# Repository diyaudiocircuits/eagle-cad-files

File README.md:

eagle-cad-files
===============

A collection of PCB (printed circuit board) designs made with the Eagle CAD program.

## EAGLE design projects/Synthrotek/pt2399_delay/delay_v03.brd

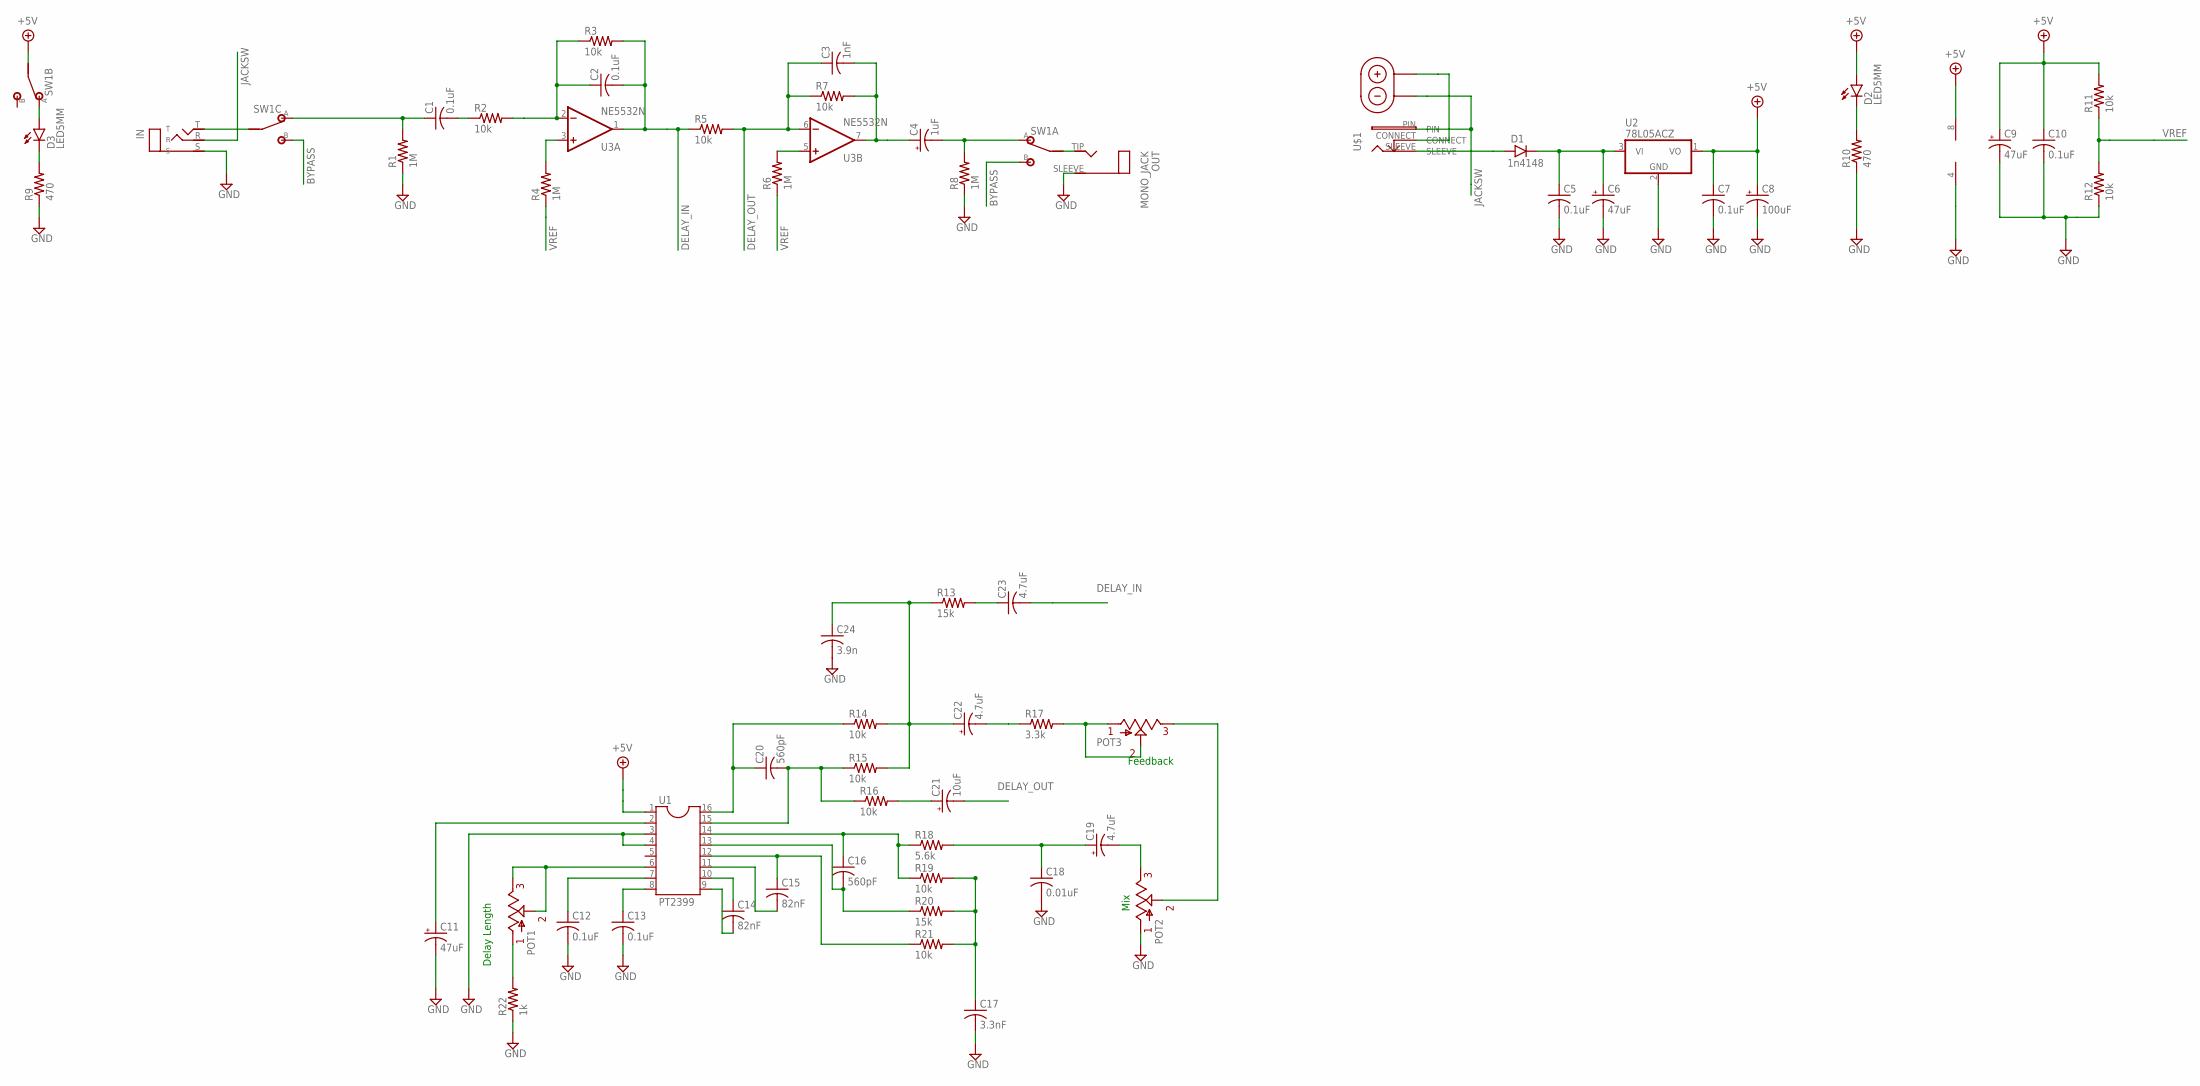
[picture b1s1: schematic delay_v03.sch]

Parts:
C1, C2, C5, C7, C10, C12, C13: 0.1uF; C050-035X075
C3: 1nF; C050-035X075
C4: 1uF; 063_025
C6, C9, C11: 47uF; 063_025
C8: 100uF; 063_025
C14, C15: 82nF; C050-035X075
C16, C20: 560pF; C050-035X075
C17: 3.3nF; C050-035X075
C18: 0.01uF; C050-035X075
C19, C22: 4.7uF; 063_025
C21: 10uF; 063_025
C23: 4.7uF; C050-035X075
C24: 3.9n; C050-035X075
D1: 1n4148; DO41-3
D2, D3: LED5MM
IN: STEREO_JACK
OUT: MONO_JACK
POT1, POT2, POT3: POT
R1, R4, R6, R8: 1M; RESISTOR
R2, R3, R5, R7, R11, R12, R14, R15, R16, R19, R21: 10k; RESISTOR
R9, R10: 470; RESISTOR
R13, R20: 15k; RESISTOR
R17: 3.3k; RESISTOR
R18: 5.6k; RESISTOR
R22: 1k; RESISTOR
SW1: 3PDT
U1: PT2399; SOCKET-16
U2: 78L05ACZ; TO-92
U3: NE5532N; DIL08
U$1: DC_JACK_OFFBOARD
U$2: 9V_BATTERY_CLIP; 9V_BATTERY

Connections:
9V: C5.1, C6.+, D1.C, U2.3 (VI)
BYPASS: SW1.A3 (B), SW1.C3 (B)
C5*: C13.1, U1.8
DELAY_IN: C2.2, C23.2, R3.2, R5.1, U3.1 (OUT)
DELAY_OUT: C3.1, C21.-, R5.2, R7.1, U3.6 (-IN)
DELAY_OUT_UNBUFFERED: R6.2, U3.5 (+IN)
GND: C5.2, C6.-, C7.2, C8.-, C9.-, C10.2, C11.-, C12.2, C13.2, C17.2, C18.2, C24.2, IN.S, OUT.SLEEVE, POT2.1, R1.1, R8.1, R9.1, R10.1, R12.1, R22.1, U1.3, U1.4, U2.2 (GND), U3.4 (V-)
JACKSW: IN.R, U$1.PIN, U$2.9V_BATTERY_-
unnamed: C23.1, R13.2
unnamed: C12.1, U1.7
unnamed: C14.2, U1.9
unnamed: C14.1, U1.10
unnamed: C17.1, R19.2, R20.2, R21.2
unnamed: C15.1, R21.1, U1.12
unnamed: POT1.2, POT1.3, U1.6
unnamed: C11.+, U1.2
unnamed: C1.1, R1.2, SW1.C1 (A)
unnamed: POT1.1, R22.2
unnamed: C16.2, R20.1, U1.13
unnamed: OUT.TIP, SW1.A2 (COM)
unnamed: C20.2, R15.1, R16.1, U1.15
unnamed: C20.1, R14.1, U1.16
unnamed: C18.1, C19.+, R18.2
unnamed: C15.2, U1.11
unnamed: C2.1, R2.2, R3.1, U3.2 (-IN)
unnamed: C19.-, POT2.3
unnamed: C22.+, C24.1, R13.1, R14.2, R15.2
unnamed: C22.-, R17.1
unnamed: C1.2, R2.1
unnamed: POT2.2, POT3.3
unnamed: C21.+, R16.2
unnamed: C16.1, R18.1, R19.1, U1.14
unnamed: D3.A, SW1.B1 (A)
unnamed: C3.2, C4.+, R7.2, U3.7 (OUT)
unnamed: D2.K (C), R10.2
unnamed: D1.A, U$1.SLEEVE
unnamed: IN.T, SW1.C2 (COM)
unnamed: C4.-, R8.2, SW1.A1 (A)
unnamed: U$1.CONNECT, U$2.9V_BATTERY_+
unnamed: D3.K (C), R9.2
unnamed: POT3.1, POT3.2, R17.2
unnamed: R4.2, U3.3 (+IN)
VA: C7.1, C8.+, C9.+, C10.1, D2.A, R11.2, SW1.B2 (COM), U1.1, U2.1 (VO), U3.8 (V+)
VREF: R4.1, R6.1, R11.1, R12.2

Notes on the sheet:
Feedback
Mix
Delay Length

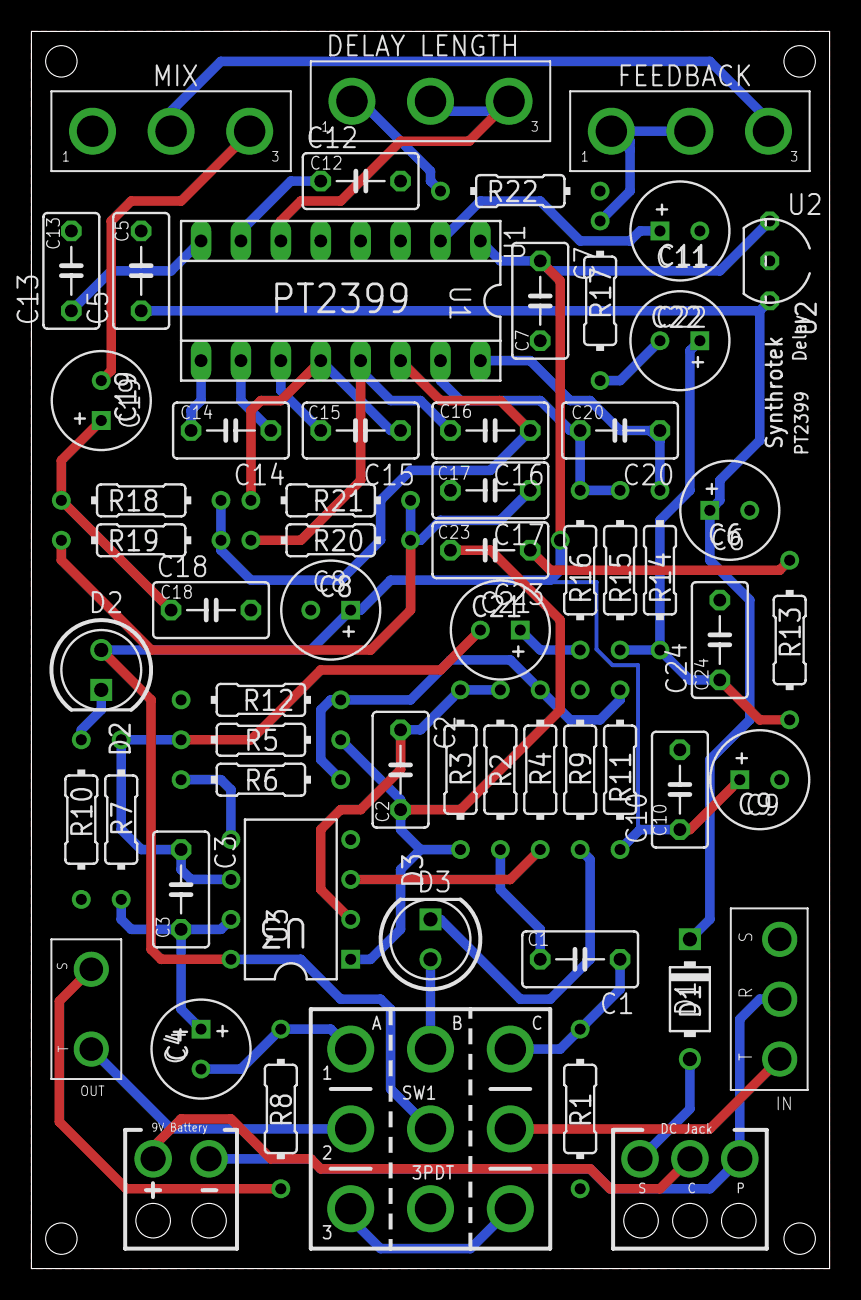
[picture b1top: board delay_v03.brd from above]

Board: 2 copper layers, 50.8 x 78.7 mm, 60 parts (0 on the bottom side), 44 nets.

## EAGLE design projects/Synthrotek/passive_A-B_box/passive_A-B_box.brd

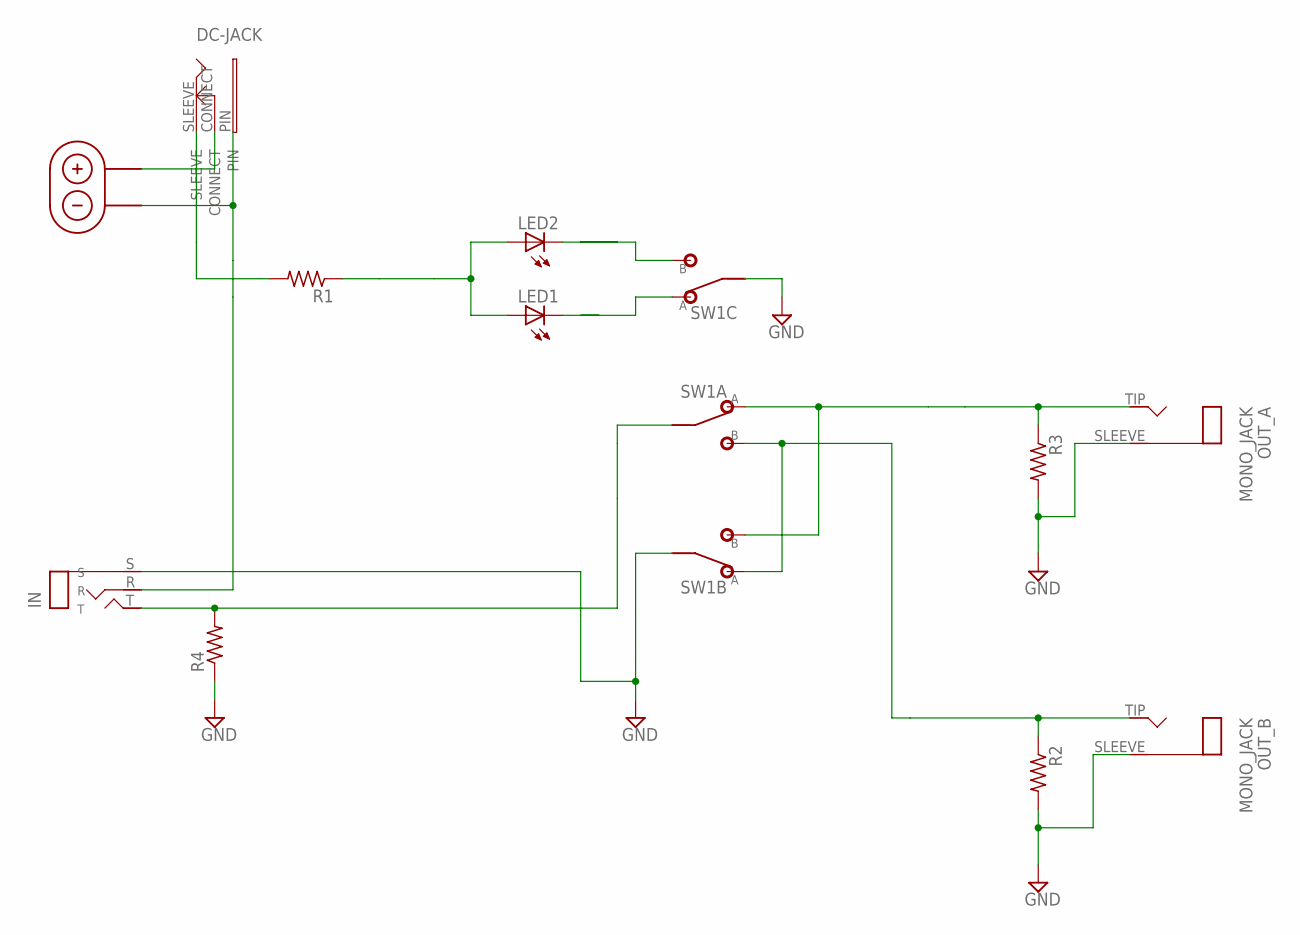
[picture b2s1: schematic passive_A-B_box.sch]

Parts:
DC-JACK: DC_JACK; DC_JACK_OFFBOARD
IN: STEREO_JACK
LED1, LED2: LED5MM
OUT_A: MONO_JACK
OUT_B: MONO_JACK
R1, R2, R3, R4: RESISTOR
SW1: 3PDT
U$4: 9V_BATTERY_CLIP; 9V_BATTERY

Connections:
DC-JACK: DC-JACK.CONNECT, U$4.9V_BATTERY_+
GND: IN.S, OUT_A.SLEEVE, OUT_B.SLEEVE, R2.2, R3.2, R4.1, SW1.B2 (COM), SW1.C2 (COM)
unnamed: IN.T, R4.2, SW1.A2 (COM)
unnamed: DC-JACK.SLEEVE, R1.2
unnamed: LED1.K (C), SW1.C1 (A)
unnamed: LED2.K (C), SW1.C3 (B)
unnamed: LED1.A, LED2.A, R1.1
unnamed: OUT_A.TIP, R3.1, SW1.A1 (A), SW1.B3 (B)
unnamed: OUT_B.TIP, R2.1, SW1.A3 (B), SW1.B1 (A)
unnamed: DC-JACK.PIN, IN.R, U$4.9V_BATTERY_-

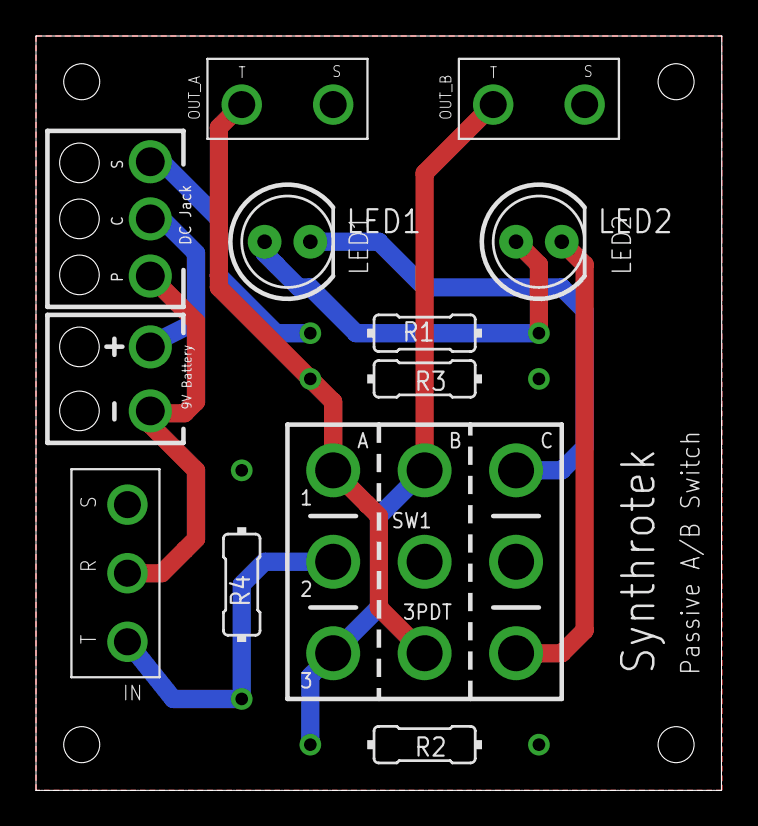
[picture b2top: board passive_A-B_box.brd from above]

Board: 2 copper layers, 38.1 x 41.9 mm, 12 parts (0 on the bottom side), 10 nets.

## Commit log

2013-05-25 All files uploaded
2013-05-25 More files uploaded...
2013-05-25 Added custom parts library and restructure for ease of access
2013-05-26 Added all libraries for project parts dependencies
